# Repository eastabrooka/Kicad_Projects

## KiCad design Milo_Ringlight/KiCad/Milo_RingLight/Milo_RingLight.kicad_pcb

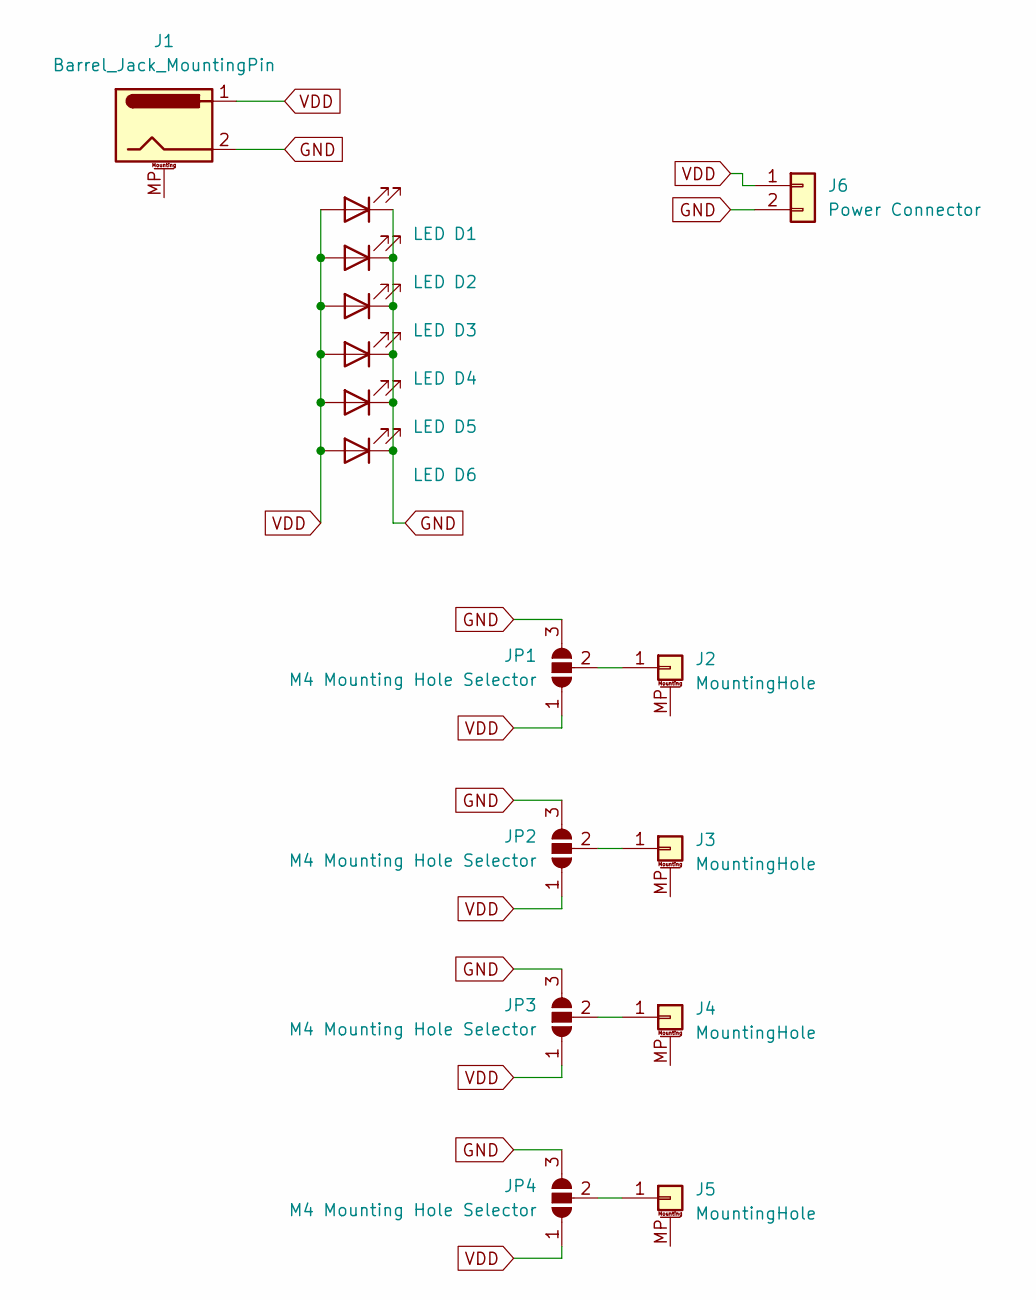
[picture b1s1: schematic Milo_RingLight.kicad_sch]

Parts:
D1, D2, D3, D4, D5, D6: LED; LED_Yuji_5730
J1: Barrel_Jack_MountingPin; BarrelJack_Wuerth_6941xx301002
J2, J3, J4, J5: MountingHole; MountingHole_4.3mm_M4_Pad_Via
J6: Power Connector; Fiducial_0.75mm_Mask2.25mm
JP1, JP2, JP3, JP4: M4 Mounting Hole Selector; SolderJumper-3_P1.3mm_Open_RoundedPad1.0x1.5mm

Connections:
GND: D1.1 (K), D2.1 (K), D3.1 (K), D4.1 (K), D5.1 (K), D6.1 (K), J1.2, J6.2, JP1.3 (B), JP2.3 (B), JP3.3 (B), JP4.3 (B)
unnamed: J2.1, JP1.2 (C)
unnamed: J3.1, JP2.2 (C)
unnamed: J4.1, JP3.2 (C)
unnamed: J5.1, JP4.2 (C)
VDD: D1.2 (A), D2.2 (A), D3.2 (A), D4.2 (A), D5.2 (A), D6.2 (A), J1.1, J6.1, JP1.1 (A), JP2.1 (A), JP3.1 (A), JP4.1 (A)

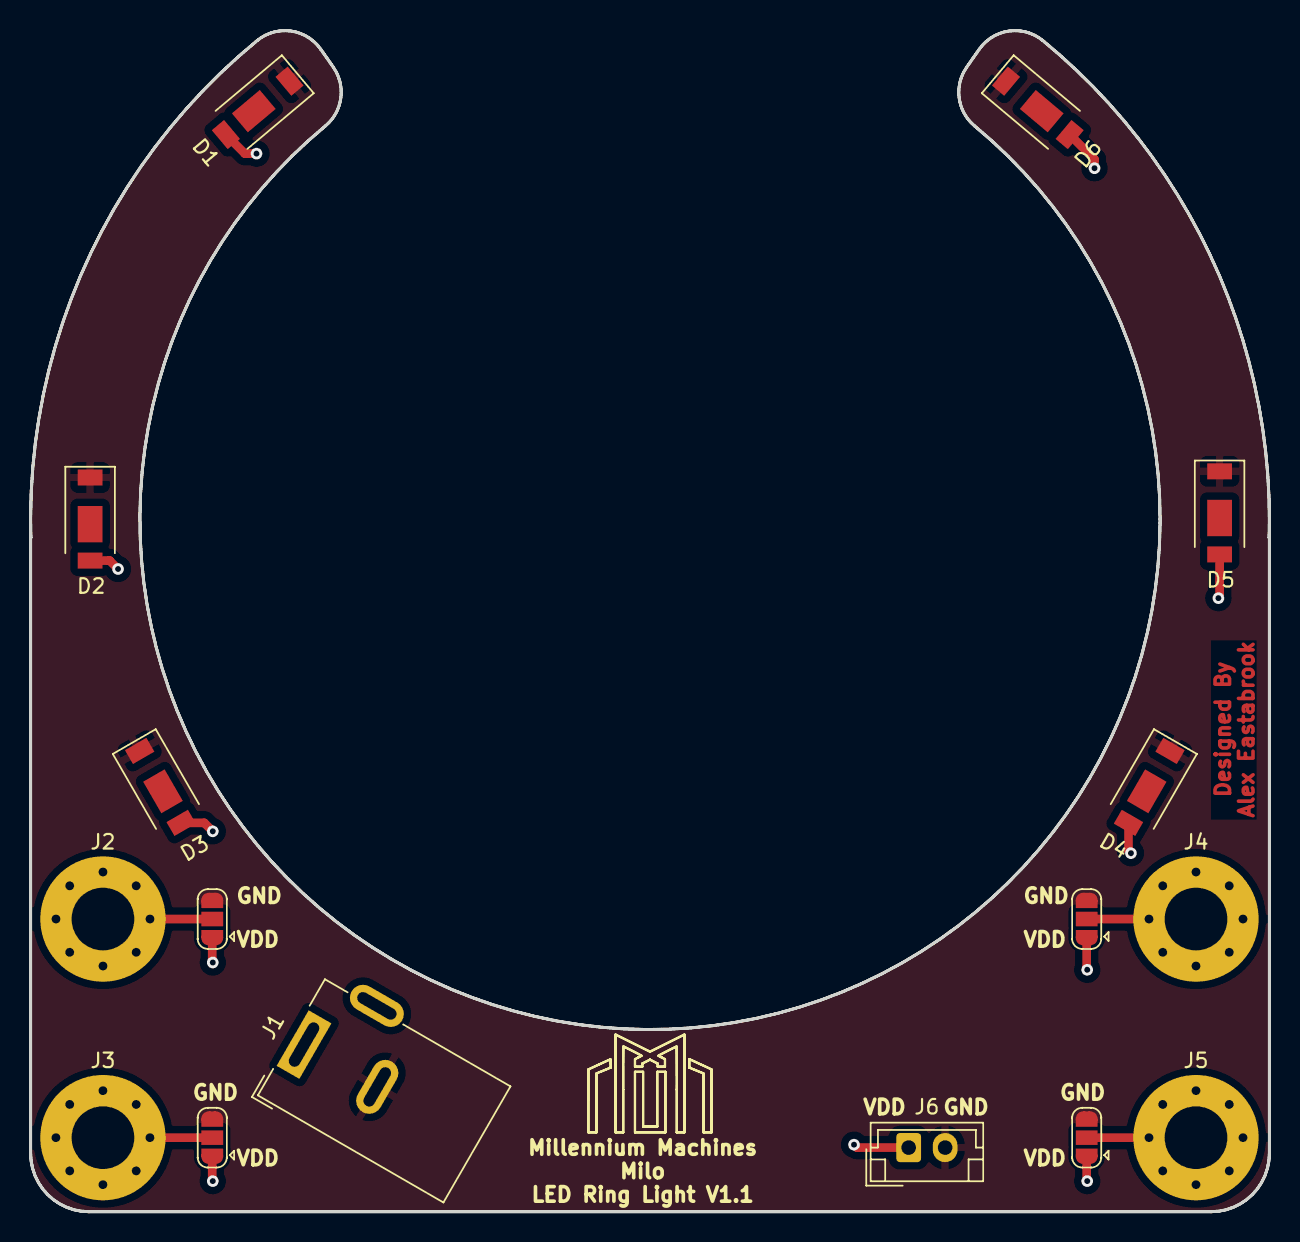
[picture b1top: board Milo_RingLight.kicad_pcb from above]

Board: 2 copper layers, 85.0 x 81.0 mm, 16 parts (0 on the bottom side), 6 nets.

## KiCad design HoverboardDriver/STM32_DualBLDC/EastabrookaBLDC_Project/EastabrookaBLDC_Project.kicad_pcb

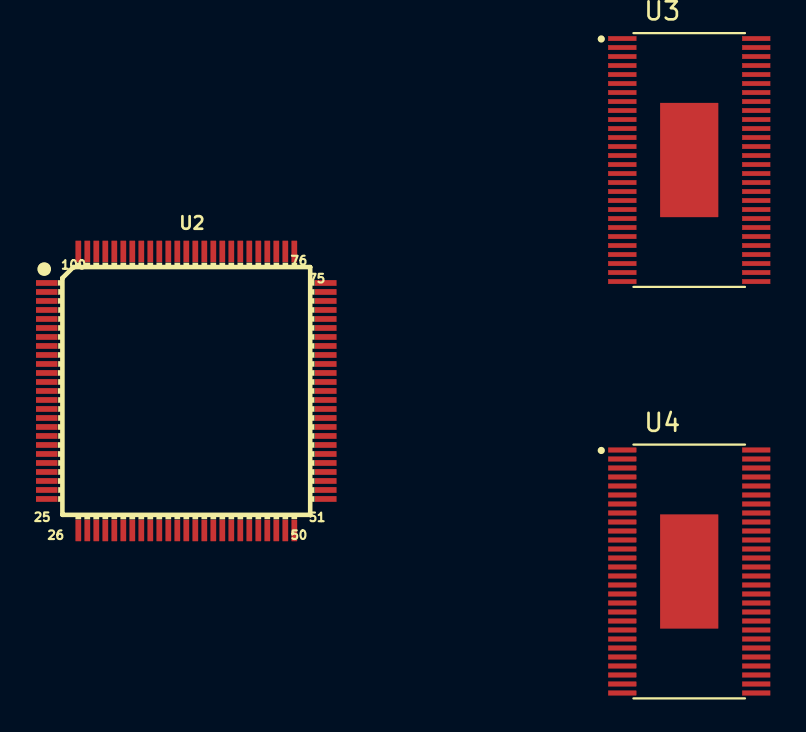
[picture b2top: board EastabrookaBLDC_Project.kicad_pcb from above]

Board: 2 copper layers, 3 parts (0 on the bottom side), 4 nets, no tracks yet.

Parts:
U2: STM32F407VET6-LQFP100; LQFP100-0.5-13.8X13.8MM
U3, U4: DRV8301DCAR; SOP50P810X120-57N

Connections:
unnamed: U3.50 (PH), U3.51 (PH)
unnamed: U3.53 (PVDD2), U3.54 (PVDD2)
unnamed: U4.50 (PH), U4.51 (PH)
unnamed: U4.53 (PVDD2), U4.54 (PVDD2)

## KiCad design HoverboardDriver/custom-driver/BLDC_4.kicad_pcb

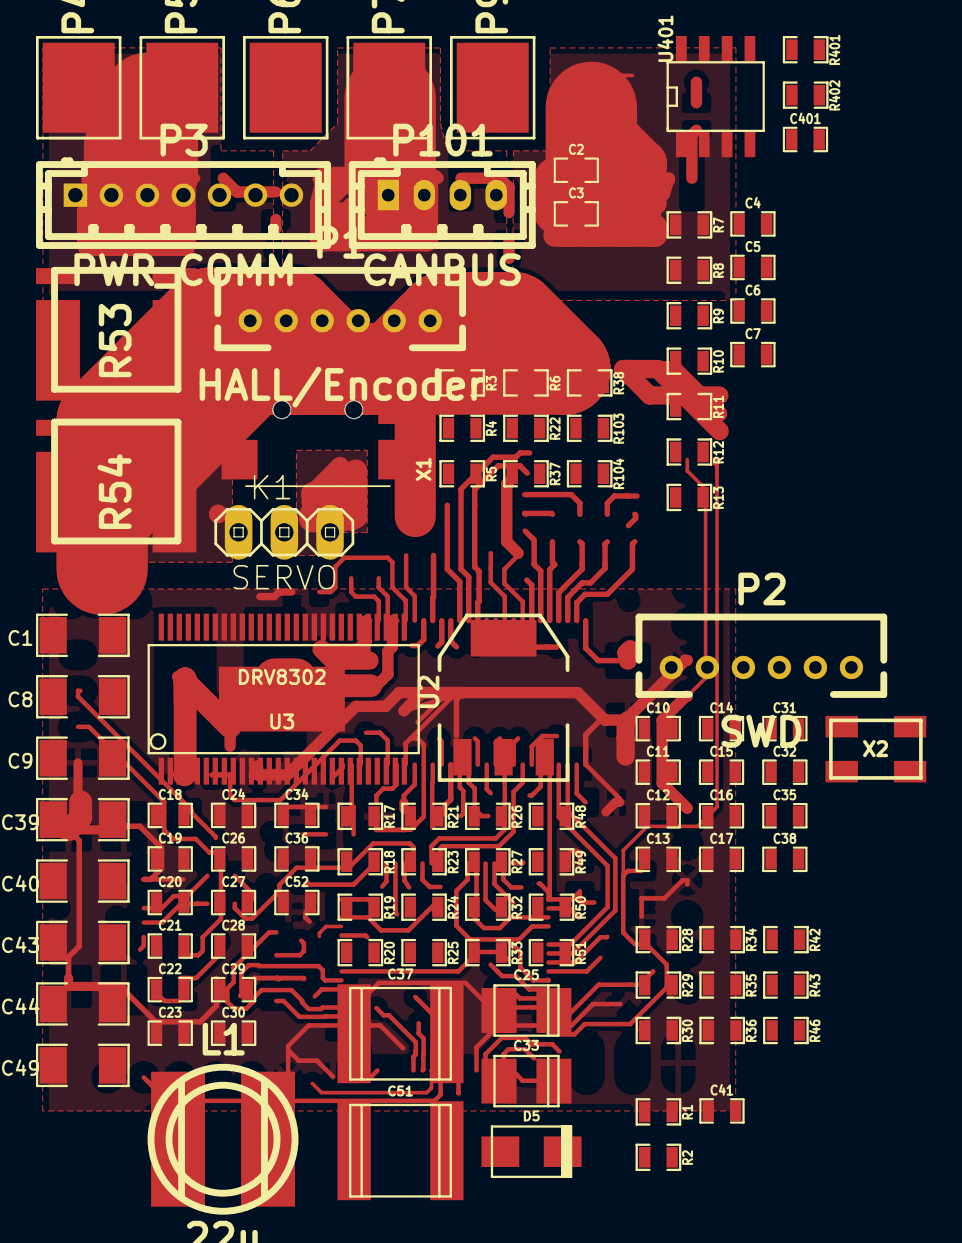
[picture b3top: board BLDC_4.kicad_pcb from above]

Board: 4 copper layers, 111 parts (0 on the bottom side), 65 nets.

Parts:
C1, C8, C9, C39, C40, C43, C44, C49: 10u,50V; SMD-1206
C2, C3, C27, C32: 100n; SMD-0603_c
C4, C5, C6, C7: 4n7; SMD-0603_c
C10, C11, C12, C13, C14, C16, C17, C18, C20, C23, C24, C26, C31, C35, C41, C52, C401: 2.2u; SMD-0603_c
C15, C38: 15p; SMD-0603_c
C19: 120p; SMD-0603_c
C21: 6.8n; SMD-0603_c
C22: 22n; SMD-0603_c
C25, C33: 100u; c_tant_B
C28, C29, C30: 220n; SMD-0603_c
C34, C36: 2.2n; SMD-0603_c
C37: 15u,100V; c_2220
C51: 15u, 100v; c_2220
D5: TVS 5V; do214ac
K1: SERVO; pinhead-1X03
L1: 22u; inductor_smd_8x5mm
P1: HALL/Encoder; MICRO_JST_6
P2: SWD; MICRO_JST_6
P3: PWR_COMM; b7b-ph-kl
P4: IN+; 1PAD_4x5mm
P5: IN-; 1PAD_4x5mm
P6: MOTOR1; 1PAD_4x5mm
P7: MOTOR2; 1PAD_4x5mm
P9: MOTOR3; 1PAD_4x5mm
P101: CANBUS; b4b-ph-kl
R1: NTC 10k; SMD-0603_r
R2, R7, R8, R9, R10, R20, R402: 10k; SMD-0603_r
R3, R23, R26, R30, R32, R36, R46: 39k; SMD-0603_r
R4, R5, R11, R12, R13, R22, R24, R27, R33: 2k2; SMD-0603_r
R6: 0R; SMD-0603_r
R17: 18k; SMD-0603_r
R18: 3k3; SMD-0603_r
R19: 15k; SMD-0603_r
R21: 220k; SMD-0603_r
R25: 1M; SMD-0603_r
R28, R29, R34, R35, R42, R43: 4R7; SMD-0603_r
R37, R38, R48, R49, R50, R51: 100R; SMD-0603_r
R53, R54: SHUNT; WSLP2726
R103, R104: 22R; SMD-0603_r
R401: NI; SMD-0603_r
U2: TC2117; SOT-223
U3: DRV8302; TSSOP-56-PP
U401: SN65HVD232; SOIC-8-W
X1: MINI-USB-SHIELD-32005-201; USB-UX60R-MB-5ST
X2: 8MHz 10ppm; Crystal_5x3mm

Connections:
+5V: C33.1, D5.2 (K), K1.2 (PM), L1.2, P1.1, P3.1, P101.4, R6.2, R17.1, U2.3 (VI)
/CAN bus transceiver/CANH: P101.3, R401.1, U401.7 (CANH)
/CAN bus transceiver/CANL: P101.2, R401.2, U401.6 (CANL)
/Filters/HALL1_IN: P1.3, R8.1, R13.1
/Filters/HALL1_OUT: C7.1, R8.2
/Filters/HALL2_IN: P1.4, R9.1, R12.1
/Filters/HALL2_OUT: C6.1, R9.2
/Filters/HALL3_IN: P1.5, R10.1, R11.1
/Filters/HALL3_OUT: C5.1, R10.2
/Filters/TEMP_MOTOR: C4.2, P1.2, R7.1
/MCU/ADC_TEMP: C41.1, R1.2, R2.1
/MCU/AN_IN: C2.2, R3.2, R4.2
/MCU/SENS1: R23.2, R24.2
/MCU/SENS2: R26.2, R27.2
/MCU/SENS3: R32.2, R33.2
/MCU/SERVO: C3.2, R5.1
/Mosfet driver/H1_LOW: R30.1, R36.1, R53.2, U3.44 (SL_A)
/Mosfet driver/H1_VS: C28.1, P9.1, R32.1, U3.46 (SH_A)
/Mosfet driver/H2_VS: C29.1, P7.1, R26.1, U3.41 (SH_B)
/Mosfet driver/H3_LOW: R46.1, R54.1, U3.34 (SL_C)
/Mosfet driver/H3_VS: C30.1, P6.1, R23.1, U3.36 (SH_C)
/Mosfet driver/M_H1: R28.2, U3.47 (GH_A)
/Mosfet driver/M_H2: R34.2, U3.42 (GH_B)
/Mosfet driver/M_H3: R42.2, U3.37 (GH_C)
/Mosfet driver/M_L1: R29.2, U3.45 (GL_A)
/Mosfet driver/M_L2: R35.2, U3.40 (GL_B)
/Mosfet driver/M_L3: R43.2, U3.35 (GL_C)
/Mosfet driver/SH1_A: R48.1, R54.3
/Mosfet driver/SH1_B: R49.1, R54.4
/Mosfet driver/SH2_A: R50.1, R53.4
/Mosfet driver/SH2_B: R51.1, R53.3
GND: C1.1, C2.1, C3.1, C4.1, C5.2, C6.2, C7.2, C8.1, C9.1, C10.1, C11.1, C12.1, C13.1, C14.1, C15.2, C16.2, C17.2, C18.2, C19.1, C20.1, C21.1, C23.1, C24.2, C25.2, C26.2, C31.1, C32.1, C33.2, C35.1, C37.1, C38.2, C39.1, C40.1, C41.2, C43.2, C44.2, C49.2, C51.1, C52.1, C401.2, D5.1 (A), K1.3, P1.6, P2.3, P3.3, P5.1, P101.1, R2.2, R4.1, R18.2, R20.2, R21.1, R24.1, R25.1, R27.1, R33.1, R53.1, R54.2, R402.2, U2.1 (GND), U3.8 (M_PWM), U3.10 (GAIN), U3.28 (AGND), U3.39 (SL_B), U3.57 (GND(POWER_PAD)), U401.2 (VSS), X1.5, X2.3 (case)
NRST: C32.2, P2.5
unnamed: C15.1, X2.1
unnamed: C21.2, R19.1
unnamed: C38.1, X2.2
unnamed: C27.1, L1.1, U3.50 (PH), U3.51 (PH)
unnamed: K1.1, R5.2
unnamed: R6.1, X1.1
unnamed: R29.1, R30.2
unnamed: R35.1, R36.2
unnamed: R43.1, R46.2
unnamed: R103.2, X1.2
unnamed: R104.2, X1.3
unnamed: C23.2, U3.27 (AVDD)
unnamed: R25.2, U3.49 (BIAS)
unnamed: C28.2, U3.48 (BST_A)
unnamed: C29.2, U3.43 (BST_B)
unnamed: C27.2, U3.52 (BST_BK)
unnamed: C30.2, U3.38 (BST_C)
unnamed: C19.2, R19.2, U3.2 (COMP)
unnamed: C22.1, U3.14 (CP1)
unnamed: C22.2, U3.15 (CP2)
unnamed: R20.1, U3.7 (DTC)
unnamed: C20.2, C52.2, U3.11 (OC_ADJ), U3.23 (DVDD)
unnamed: C18.1, C26.1, U3.13 (GVDD)
unnamed: R21.2, U3.1 (RT_CLK)
unnamed: C34.1, R48.2, U3.33 (SN1)
unnamed: C36.1, R50.2, U3.31 (SN2)
unnamed: C34.2, R49.2, U3.32 (SP1)
unnamed: C36.2, R51.2, U3.30 (SP2)
unnamed: R17.2, R18.1, U3.3 (VSENSE)
unnamed: R402.1, U401.8 (Rs)
VCC: C10.2, C11.2, C12.2, C13.2, C14.2, C24.1, C25.1, C31.2, C35.2, C401.1, P2.1, P3.2, R1.1, R7.2, R11.2, R12.2, R13.2, R22.2, U2.2 (VO), U3.9 (M_OC), U3.24 (REF), U401.3 (VDD)
V_SUPPLY: C1.2, C8.2, C9.2, C37.2, C39.2, C40.2, C43.1, C44.1, C49.1, C51.2, P4.1, R3.1, U3.29 (PVDD1), U3.53 (PVDD2), U3.54 (PVDD2)

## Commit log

2024-01-31 WIP - Milo LED ring light.
2024-01-31 Continued Work.
2024-01-31 Add Ignore file.
2024-01-31 Sent to Fab.
2024-02-03 Add in Submodule.
2024-02-03 Rip out Submodule to Here - Start customising.
2024-02-04 Start of Ripup and Modify
2024-02-04 New Project, SnapEDA Footprints.
2024-02-05 Idk what these deltas are.
2024-02-05 Include Fets.
2024-02-19 Champion Idiot. Forgot to generate Drills.
